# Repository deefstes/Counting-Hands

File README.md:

# Counting-Hands
Arduino UNO based circuit that drives servos to raise/lower the fingers of two hands to serve as a countdown timer.

This project consists of three parts, split over three folders:
Electronics - KiCAD project for the circuit schematics and PCB design of a shield that fits an Arduino UNO
Software    - Arduino source code
Woodworking - SketchUp project for physical design of the countdown timer

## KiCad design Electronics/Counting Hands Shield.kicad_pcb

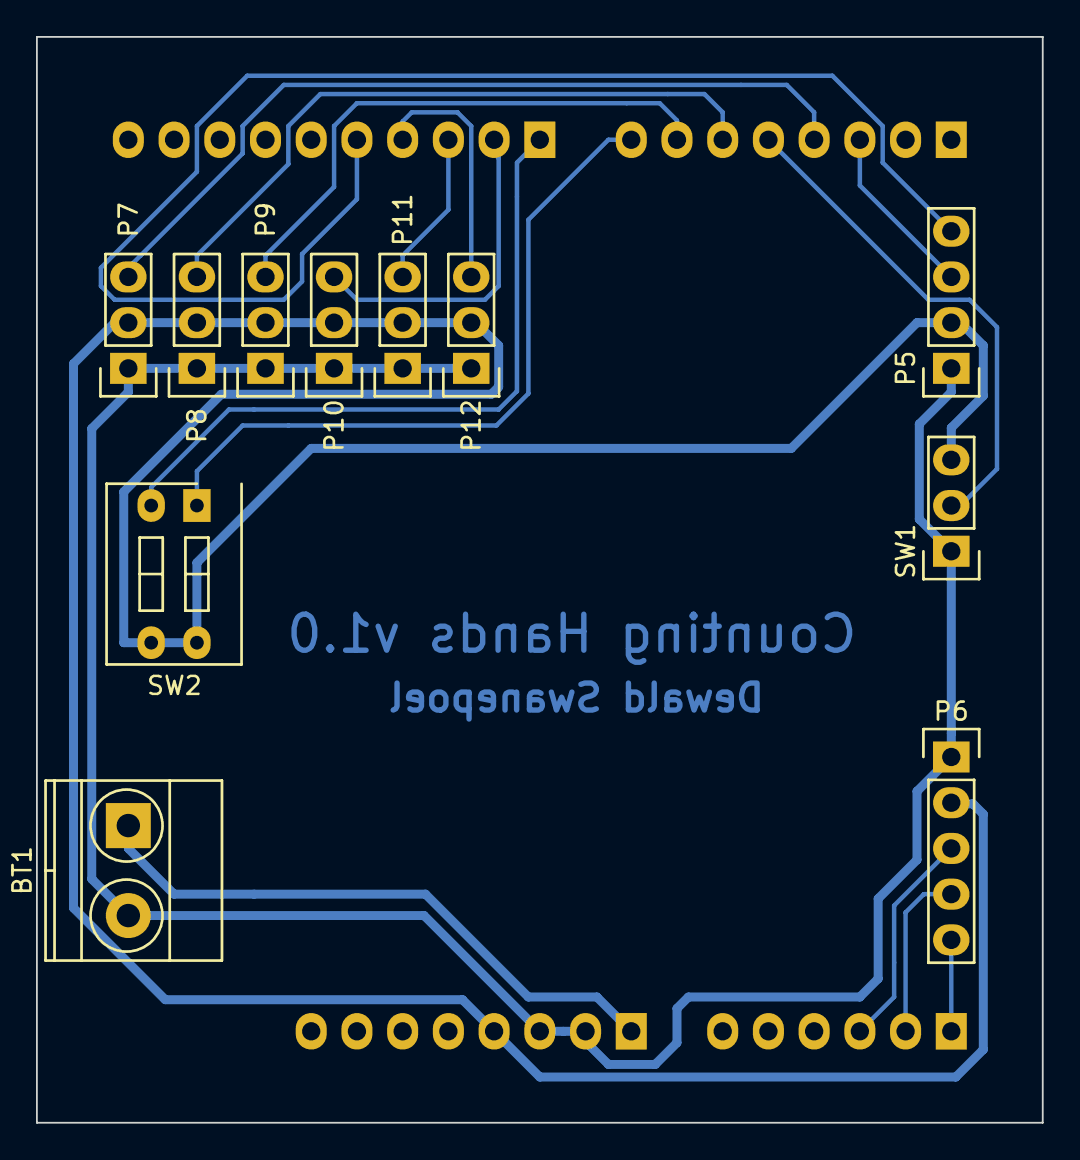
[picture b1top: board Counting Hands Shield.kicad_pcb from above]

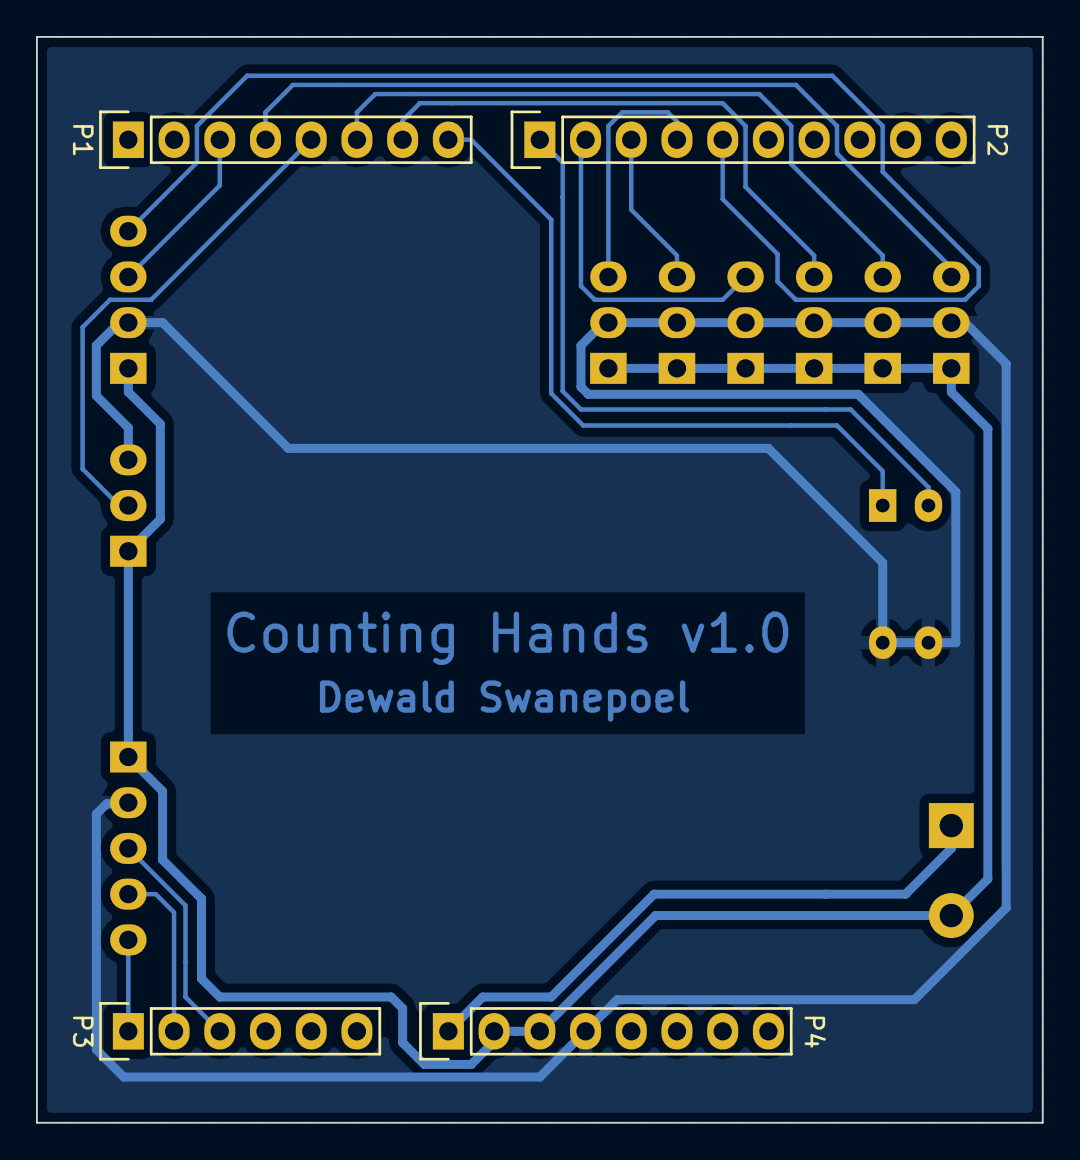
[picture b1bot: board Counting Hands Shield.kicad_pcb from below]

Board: 2 copper layers, 55.9 x 60.3 mm, 15 parts (4 on the bottom side), 17 nets.

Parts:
BT1: 7-12V; TerminalBlock_Pheonix_MKDS1.5-2pol
P1: Arduino P0-P7; Pin_Header_Straight_1x08
P2: Arduino P8-SCL; Pin_Header_Straight_1x10
P3: Arduino A5-A0; Pin_Header_Straight_1x06
P4: Arduino Vin-Blank; Pin_Header_Straight_1x08
P5: 4x7 Segment Display; Pin_Header_Straight_1x04
P6: Rotary; Pin_Header_Straight_1x05
P7: Servo_H; Pin_Header_Straight_1x03
P8: Servo_1; Pin_Header_Straight_1x03
P9: Servo_2; Pin_Header_Straight_1x03
P10: Servo_3; Pin_Header_Straight_1x03
P11: Servo_4; Pin_Header_Straight_1x03
P12: Servo_5; Pin_Header_Straight_1x03
SW1: Direction; Pin_Header_Straight_1x03
SW2: Default Interval; SW_DIP_x2_Slide

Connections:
/5V: P4.4, P5.2, P6.2, P7.2, P8.2, P9.2, P10.2, P11.2, P12.2, SW1.3, SW2.3, SW2.4
/GND: BT1.2, P4.2, P4.3, P5.1, P6.1, P7.1, P8.1, P9.1, P10.1, P11.1, P12.1, SW1.1
/Vin: BT1.1, P4.1
unnamed: P1.3, P5.3
unnamed: P1.4, P7.3
unnamed: P1.5, SW1.2
unnamed: P1.6, P8.3
unnamed: P1.7, P9.3
unnamed: P1.8, SW2.1
unnamed: P2.1, SW2.2
unnamed: P2.5, P5.4
unnamed: P3.1, P6.5
unnamed: P3.2, P6.4
unnamed: P3.3, P6.3
unnamed: P2.2, P10.3
unnamed: P2.3, P11.3
unnamed: P2.4, P12.3

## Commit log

2016-12-22 Added all files to project
2016-12-22 Changes to KiCAD project
    Replaced Potentiometer (VR1) with Rotary Encoder (P6)
    Added 2DIP switch for default interval
    Replaced 8 LEDs progress indicator and 74HC595 Shift Register with 4 digit 7 Segment Display
2016-12-22 Changes to KiCAD project
    Tidied up schematic and PCB
2016-12-23 Moved arduino sketch into folder with the same name, which is a requirement for Arduino sketches.
2019-04-28 Changed pinout for rotary encoder
2019-04-28 Added veroboard Fritzing layout
2019-04-28 Opened and saved project in newer version of KiCad
